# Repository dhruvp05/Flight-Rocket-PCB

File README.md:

# PCB for model Flight Rocket

### PCB Schematic

### PCB Layout

### 3D Front view

### 3D Back view

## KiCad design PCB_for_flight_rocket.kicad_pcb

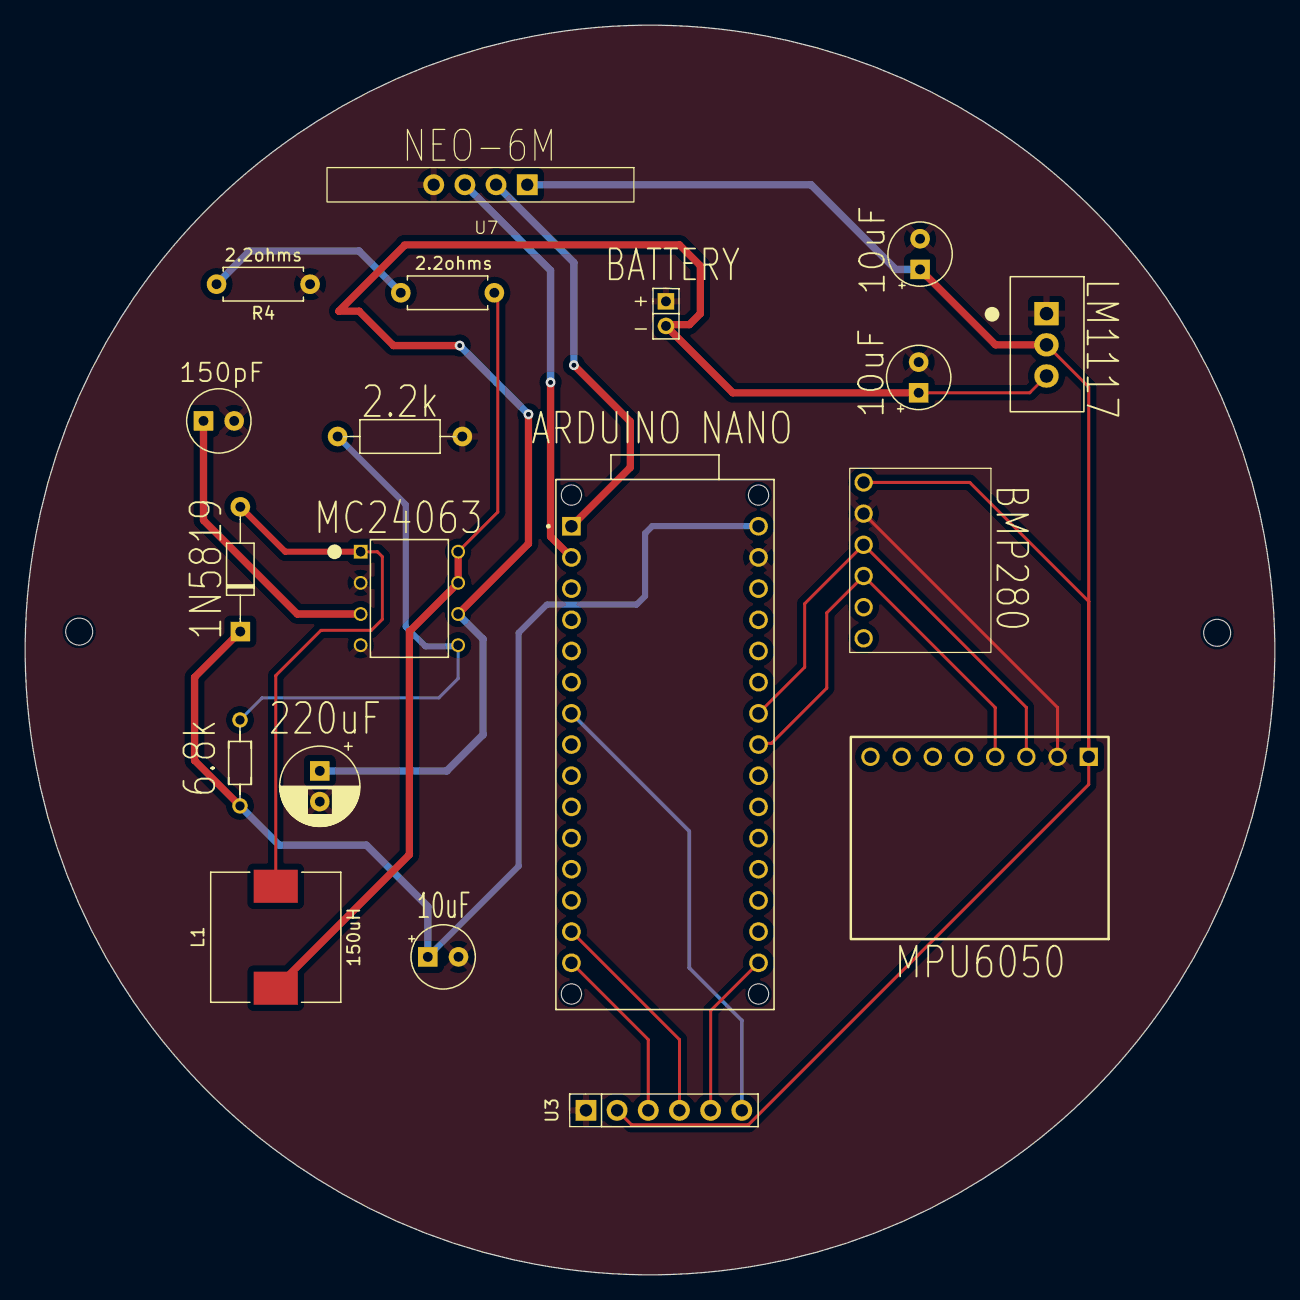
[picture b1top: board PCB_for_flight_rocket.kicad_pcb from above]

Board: 2 copper layers, 101.8 x 101.8 mm, 19 parts (0 on the bottom side), 17 nets.

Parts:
BT1: Battery
C1: 220uF; Capacitor_220uF
C2, C3, C5: 10uF; capacitor_10uF
C4: 150pF; Capacitor_47nF
D1: 1N5819
L1: 150uH; L_10.4x10.4_H4.8
R1, R4: 2.2ohms; R_Axial_DIN0207_L6.3mm_D2.5mm_P7.62mm_Horizontal
R2: 6.8k; resistor_6.8k
R3: 2.2k; resistor_2.2k
U1: MC34063AP; MC34063
U2: LM1117T-3.3; LM1117
U3: PinSocket_1x06_P2.54mm_Vertical
U4: A000005; MODULE_ABX00053
U5: MPU6050
U6: BMP280
U7: Neo-6M

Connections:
3.3V: C3.1, U2.2 (VO), U3.2 (Vcc), U5.1 (VCC), U6.1 (Vcc), U7.1 (Vcc)
5V: C5.1, D1.1 (K), R2.1, U4.30 (VIN)
+3.7V: BT1.2 (-), C1.1, C2.1, U1.6 (VCC), U2.3 (VI)
CS_SDC: U3.6 (CS), U4.7 (D4)
GND: BT1.1 (+), C1.2, C2.2, C3.2, C4.2, C5.2, R3.2, R4.1, U1.2 (SW_E), U1.4 (GND), U2.1 (GND), U3.1 (GND), U4.29 (GND_2), U5.2 (GND), U6.2 (GND), U7.4 (GND)
GPS_RX: U4.1 (D0/TX), U7.2 (Rx)
GPS_TX: U4.2 (D1/RX), U7.3 (Tx)
MISO_SDC: U3.3 (MISO), U4.15 (D12)
MOSI_SDC: U3.4 (MOSI), U4.14 (D11)
unnamed: D1.2 (A), L1.2, U1.1 (SW_C)
unnamed: R1.1, R4.2
unnamed: R2.2, R3.1, U1.5 (COMPARATOR_NEG)
unnamed: C4.1, U1.3 (CT)
unnamed: L1.1, R1.2, U1.7 (IPK), U1.8 (DRVR_C)
SCK: U4.24 (A5), U5.3 (SCL), U6.3 (SCK)
SCK_SDC: U3.5 (SCK), U4.16 (D13)
SDA: U4.23 (A4), U5.4 (SDA), U6.4 (SDA)

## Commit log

2024-03-21 Pictures of layout and 3D view
2024-03-21 Added ground plane
